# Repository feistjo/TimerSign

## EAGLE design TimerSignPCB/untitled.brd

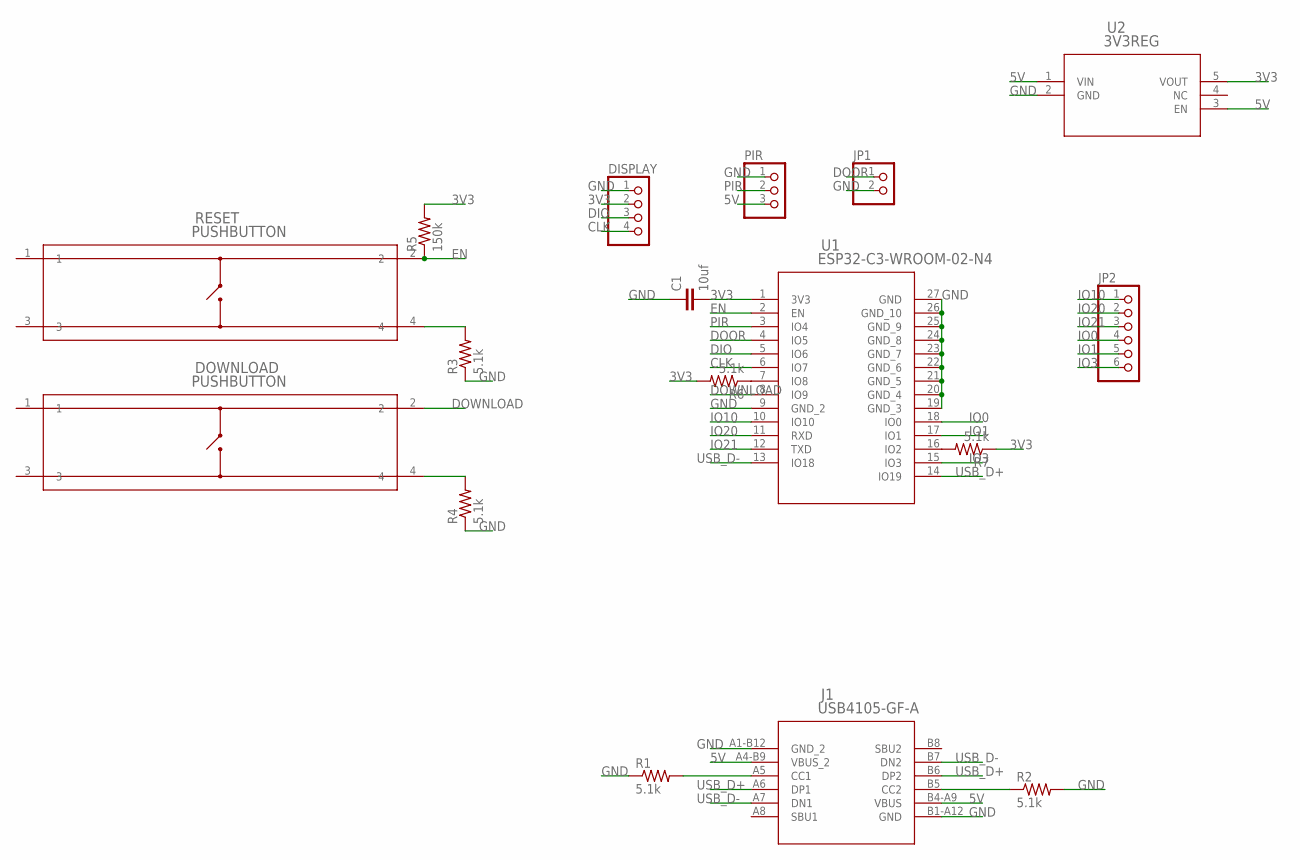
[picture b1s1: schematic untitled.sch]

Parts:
C1: 10uf; C0805
DISPLAY: PINHD-1X4; 1X04
DOWNLOAD: PUSHBUTTON; SW4_PTS815_SJM_250_SMTR_LFS_CN
J1: USB4105-GF-A; USB4105_GCT
JP1: PINHD-1X2; 1X02
JP2: PINHD-1X6; 1X06
PIR: PINHD-1X3; 1X03
R1, R2, R3, R4, R6, R7: 5.1k; R0603
R5: 150k; R0603
RESET: PUSHBUTTON; SW4_PTS815_SJM_250_SMTR_LFS_CN
U1: ESP32-C3-WROOM-02-N4; IC18_ESP32-C3-WROOM-02-N4_EXP
U2: 3V3REG; SOT_RG1_DIO

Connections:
3V3: C1.2, DISPLAY.2, R5.2, R6.2, R7.1, U1.1 (3V3), U2.5 (VOUT)
5V: J1.A4-B9 (VBUS_2), J1.B4-A9 (VBUS), PIR.3, U2.1 (VIN), U2.3 (EN)
CLK: DISPLAY.4, U1.6 (IO7)
DIO: DISPLAY.3, U1.5 (IO6)
DOOR: JP1.1, U1.4 (IO5)
DOWNLOAD: DOWNLOAD.2, U1.8 (IO9)
EN: R5.1, RESET.2, U1.2 (EN)
GND: C1.1, DISPLAY.1, J1.A1-B12 (GND_2), J1.B1-A12 (GND), JP1.2, PIR.1, R1.1, R2.2, R3.1, R4.1, U1.9 (GND_2), U1.19 (GND_3), U1.20 (GND_4), U1.21 (GND_5), U1.22 (GND_6), U1.23 (GND_7), U1.24 (GND_8), U1.25 (GND_9), U1.26 (GND_10), U1.27 (GND), U2.2 (GND)
IO0: JP2.4, U1.18 (IO0)
IO1: JP2.5, U1.17 (IO1)
IO3: JP2.6, U1.15 (IO3)
IO10: JP2.1, U1.10 (IO10)
IO20: JP2.2, U1.11 (RXD)
IO21: JP2.3, U1.12 (TXD)
unnamed: R6.1, U1.7 (IO8)
unnamed: R7.2, U1.16 (IO2)
unnamed: J1.A5 (CC1), R1.2
unnamed: DOWNLOAD.4, R4.2
unnamed: J1.B5 (CC2), R2.1
unnamed: R3.2, RESET.4
PIR: PIR.2, U1.3 (IO4)
USB_D+: J1.A6 (DP1), J1.B6 (DP2), U1.14 (IO19)
USB_D-: J1.A7 (DN1), J1.B7 (DN2), U1.13 (IO18)

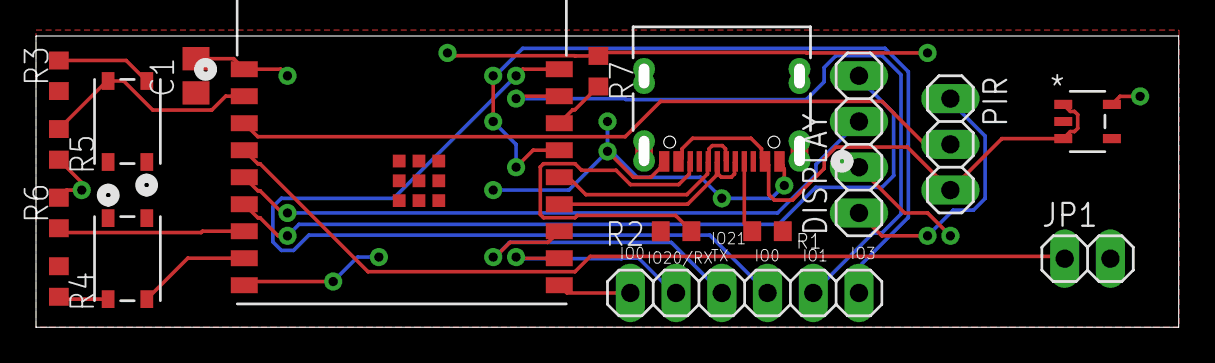
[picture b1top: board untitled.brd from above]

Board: 2 copper layers, 62.9 x 15.6 mm, 17 parts (0 on the bottom side), 23 nets.

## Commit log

2023-05-15 Initial
2023-06-05 Much code
2023-06-05 wifi auth update
2023-06-05 gitignore attempt
2023-06-05 gitignore attempt, pcb things
2023-06-05 gitignore fix
2023-06-06 Working with eduroam, button presses to display IP, websockets and webpage working

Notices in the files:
parts and their libraries:
COPYRIGHT: Copyright (C) 2023 Ultra Librarian. All rights reserved.
